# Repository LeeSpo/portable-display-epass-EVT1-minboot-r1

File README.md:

# Portable Display ePass

当前自研硬件为 **38 × 64 mm、四层 split-power 工程候选**，尚未放行生产。

- [打开当前 KiCad 工程与运行验证](portable-display/hardware/v1-WEB6-redesign/split-power-candidate/README_CN.md)
- [未完成项与实板验收](portable-display/hardware/v1-WEB6-redesign/split-power-candidate/OPEN_ISSUES_CN.md)
- [JLC 报价/预览包（未放行）](portable-display/hardware/v1-WEB6-redesign/split-power-candidate/verification/production_20261015/README_CN.md)
- [开发板学习资料](portable-display/hardware/v2-dev-board/README_CN.md)
- [项目进展、分支与旧稿恢复](portable-display/docs/PROJECT_STATUS_CN.md)

仓库只保留最新工程和验证包。旧版本、布线试验和历史报告通过 Git 历史追溯；不重写历史。

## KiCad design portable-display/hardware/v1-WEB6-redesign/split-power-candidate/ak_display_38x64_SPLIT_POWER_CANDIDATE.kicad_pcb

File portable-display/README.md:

# Portable Display

当前硬件为 38 × 64 mm 四层工程候选。电源冷启动、屏幕装配和实板功能尚未验收，**未放行投板、贴片或上电**。

| 入口 | 内容 |
|---|---|
| [当前自研工程](hardware/v1-WEB6-redesign/split-power-candidate/README_CN.md) | 原理图、PCB、本地库、约束及独立验证工具 |
| [当前工程验收记录](hardware/v1-WEB6-redesign/split-power-candidate/OPEN_ISSUES_CN.md) | 尚未关闭的工程与实板事项 |
| [开发板资料](hardware/v2-dev-board/README_CN.md) | YuzukiHD-Lizard 文档和图片，不是自研板的下一硬件版本 |
| [产品和屏幕资料](docs/README.md) | 屏幕规范、机械装配评估和项目状态 |
| [原始参考资料](reference/README.md) | 芯片/连接器资料、原始引脚表 |

工程使用 `${KIPRJMOD}` 本地库。运行命令见当前工程 README；无需历史硬件目录。

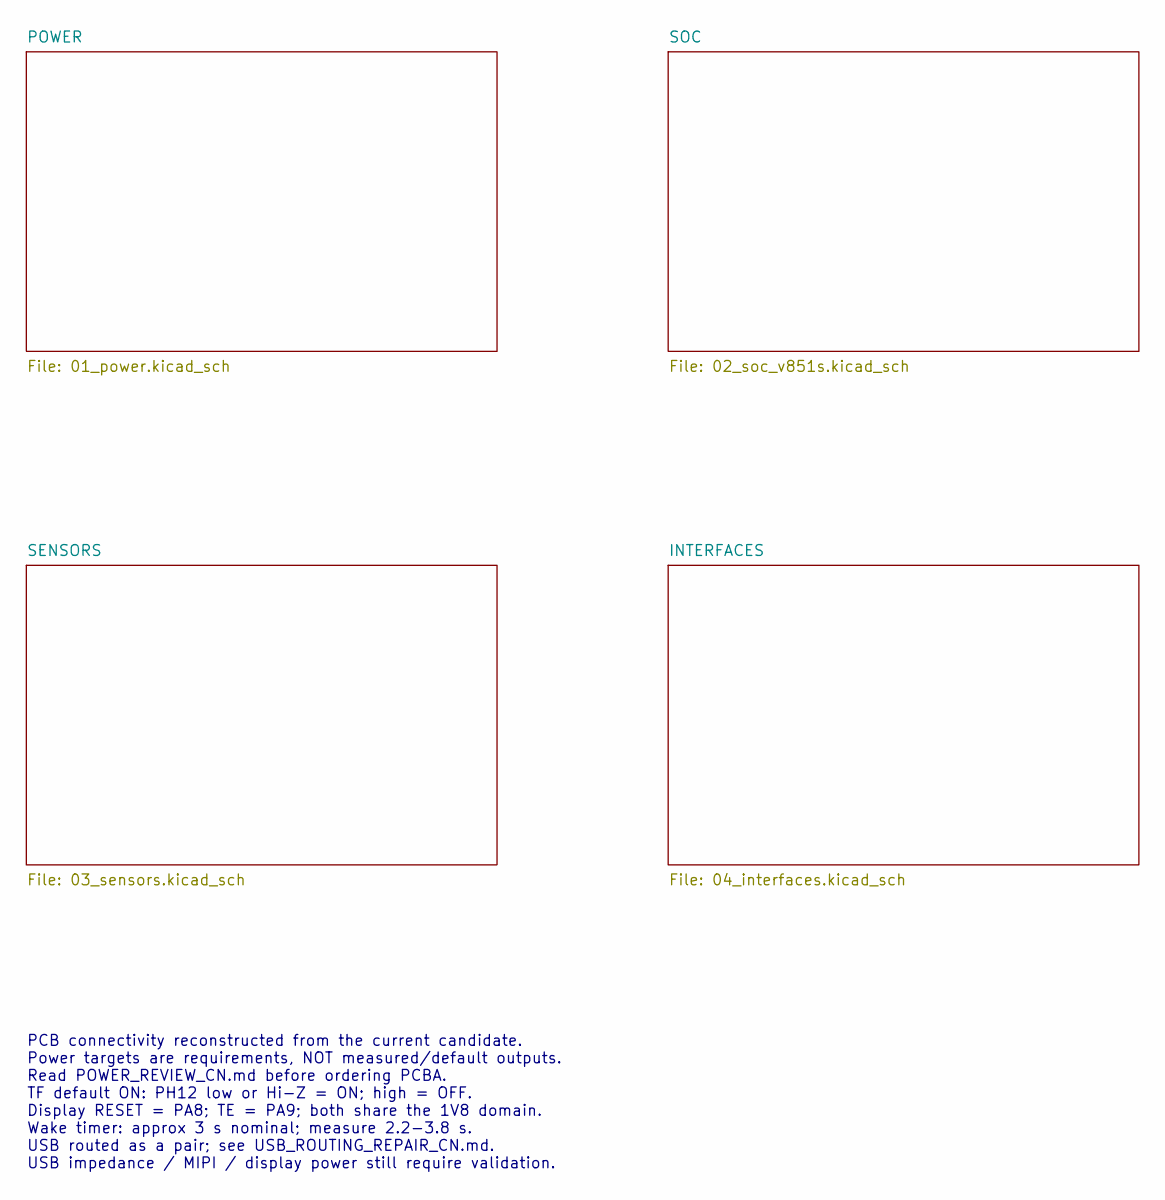
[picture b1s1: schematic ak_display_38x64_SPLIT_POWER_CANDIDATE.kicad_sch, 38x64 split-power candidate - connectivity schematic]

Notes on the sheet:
PCB connectivity reconstructed from the current candidate. Power targets are requirements, NOT measured/default outputs. Read POWER_REVIEW_CN.md before ordering PCBA. TF default ON: PH12 low or Hi-Z = ON; high = OFF. Display RESET = PA8; TE = PA9; both share the 1V8 domain. Wake timer: approx 3 s n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

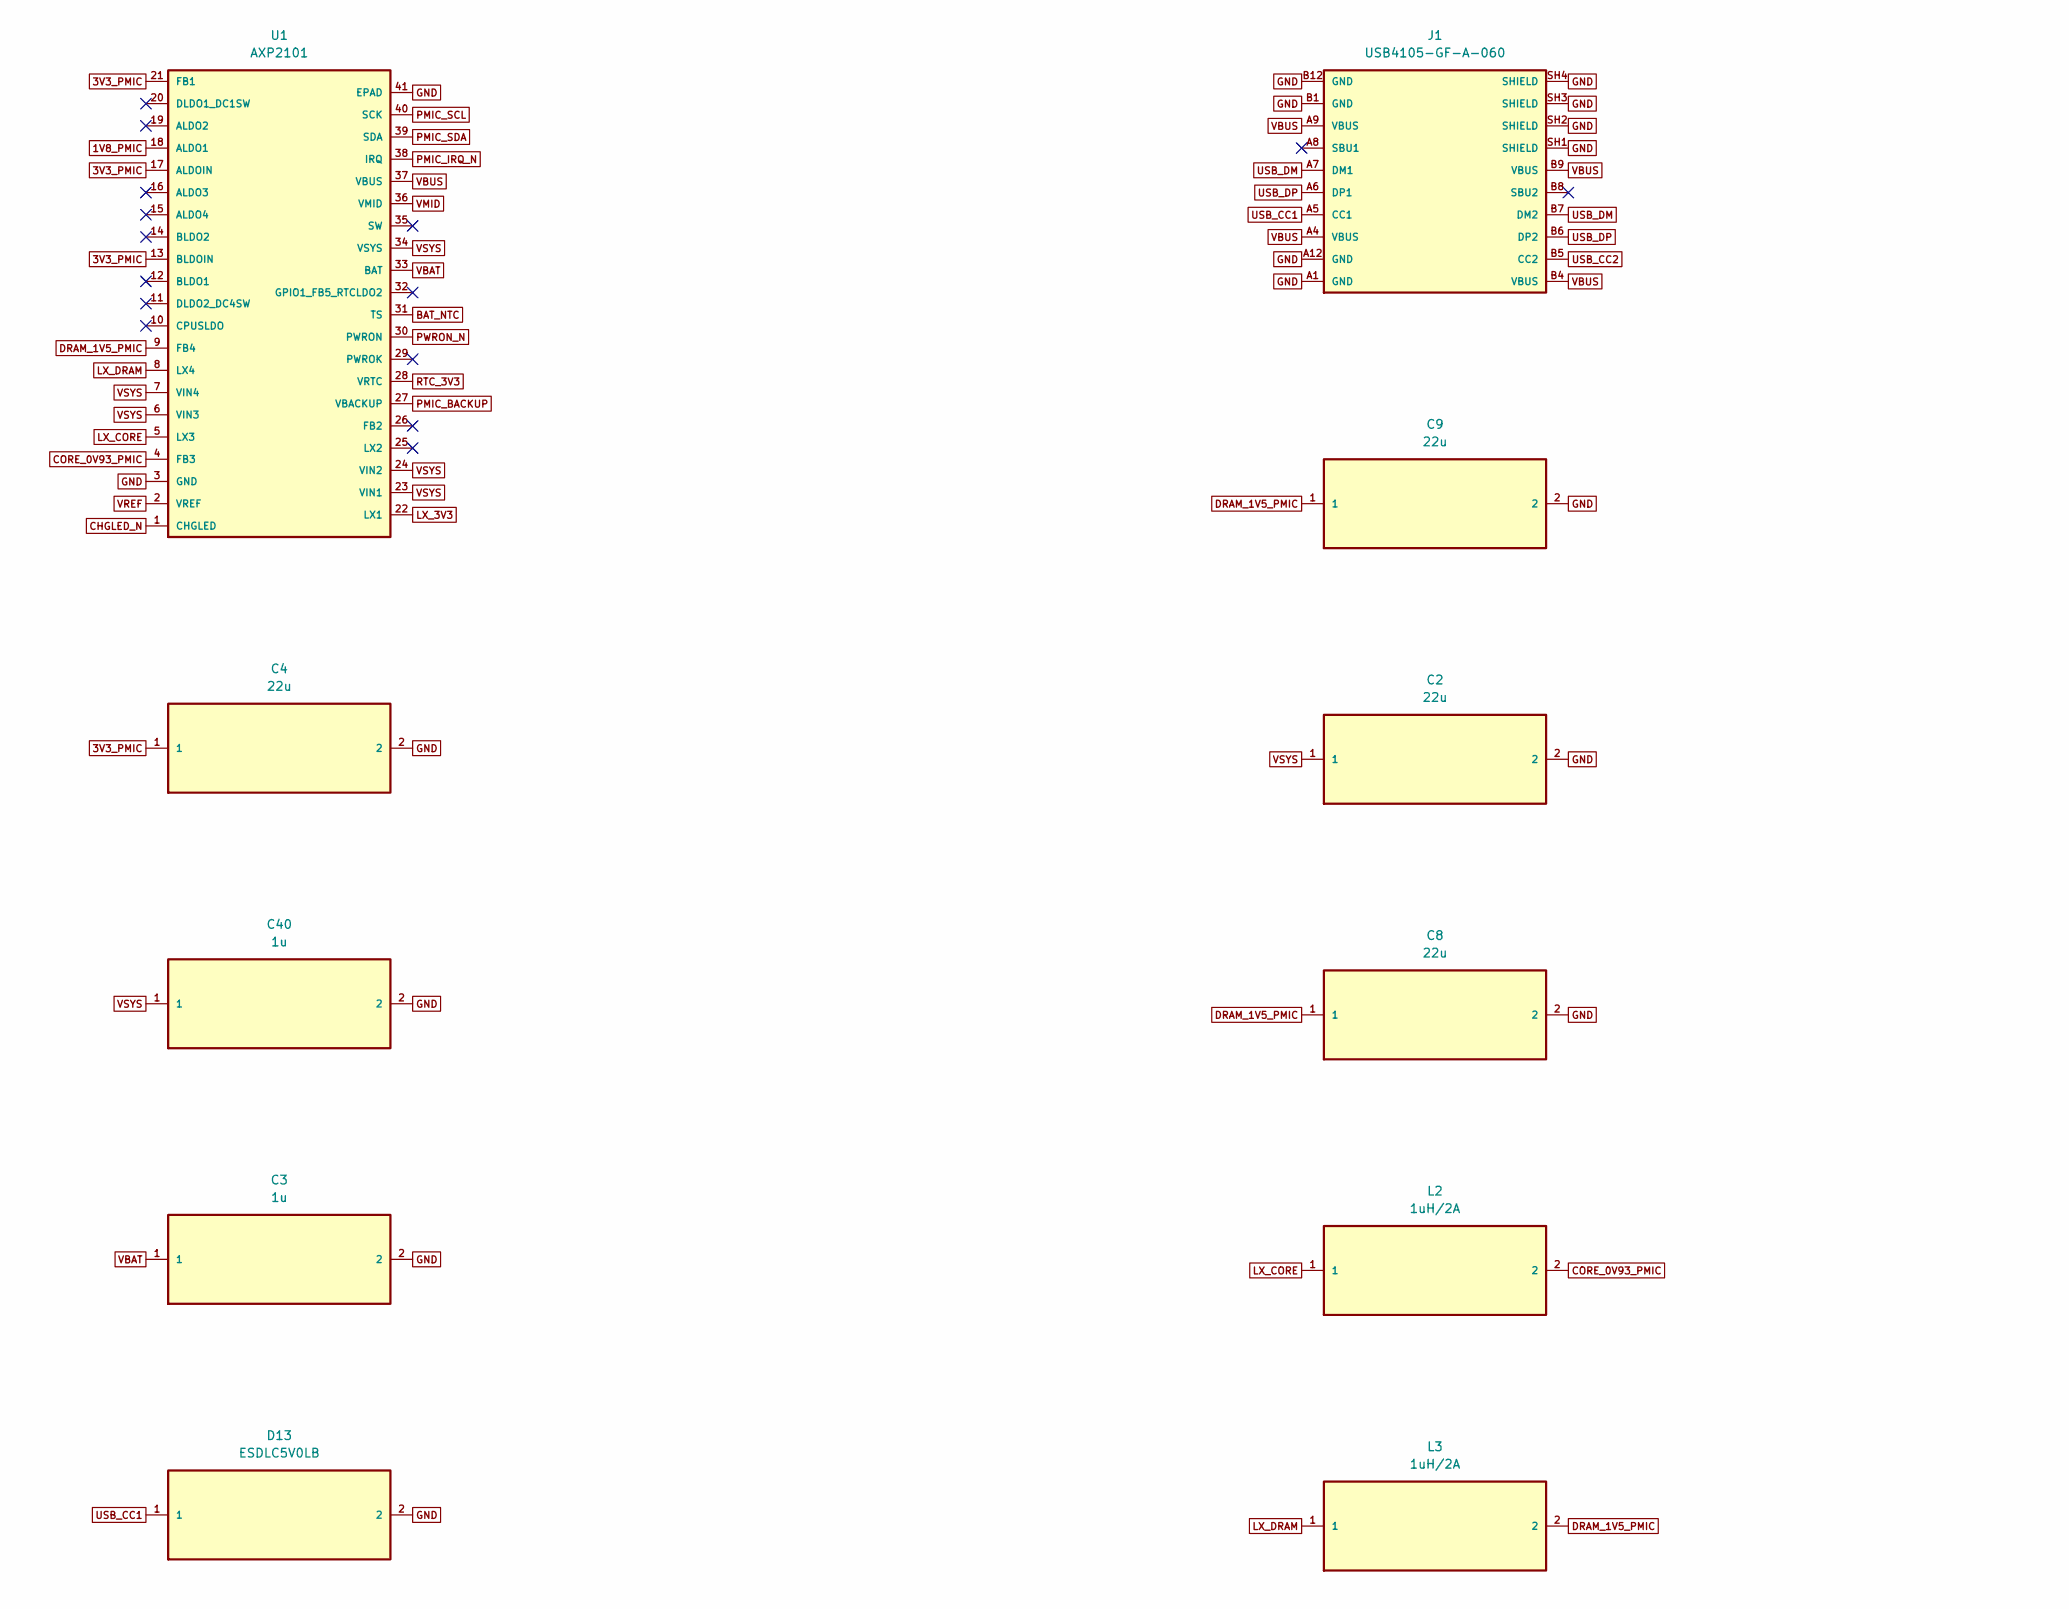
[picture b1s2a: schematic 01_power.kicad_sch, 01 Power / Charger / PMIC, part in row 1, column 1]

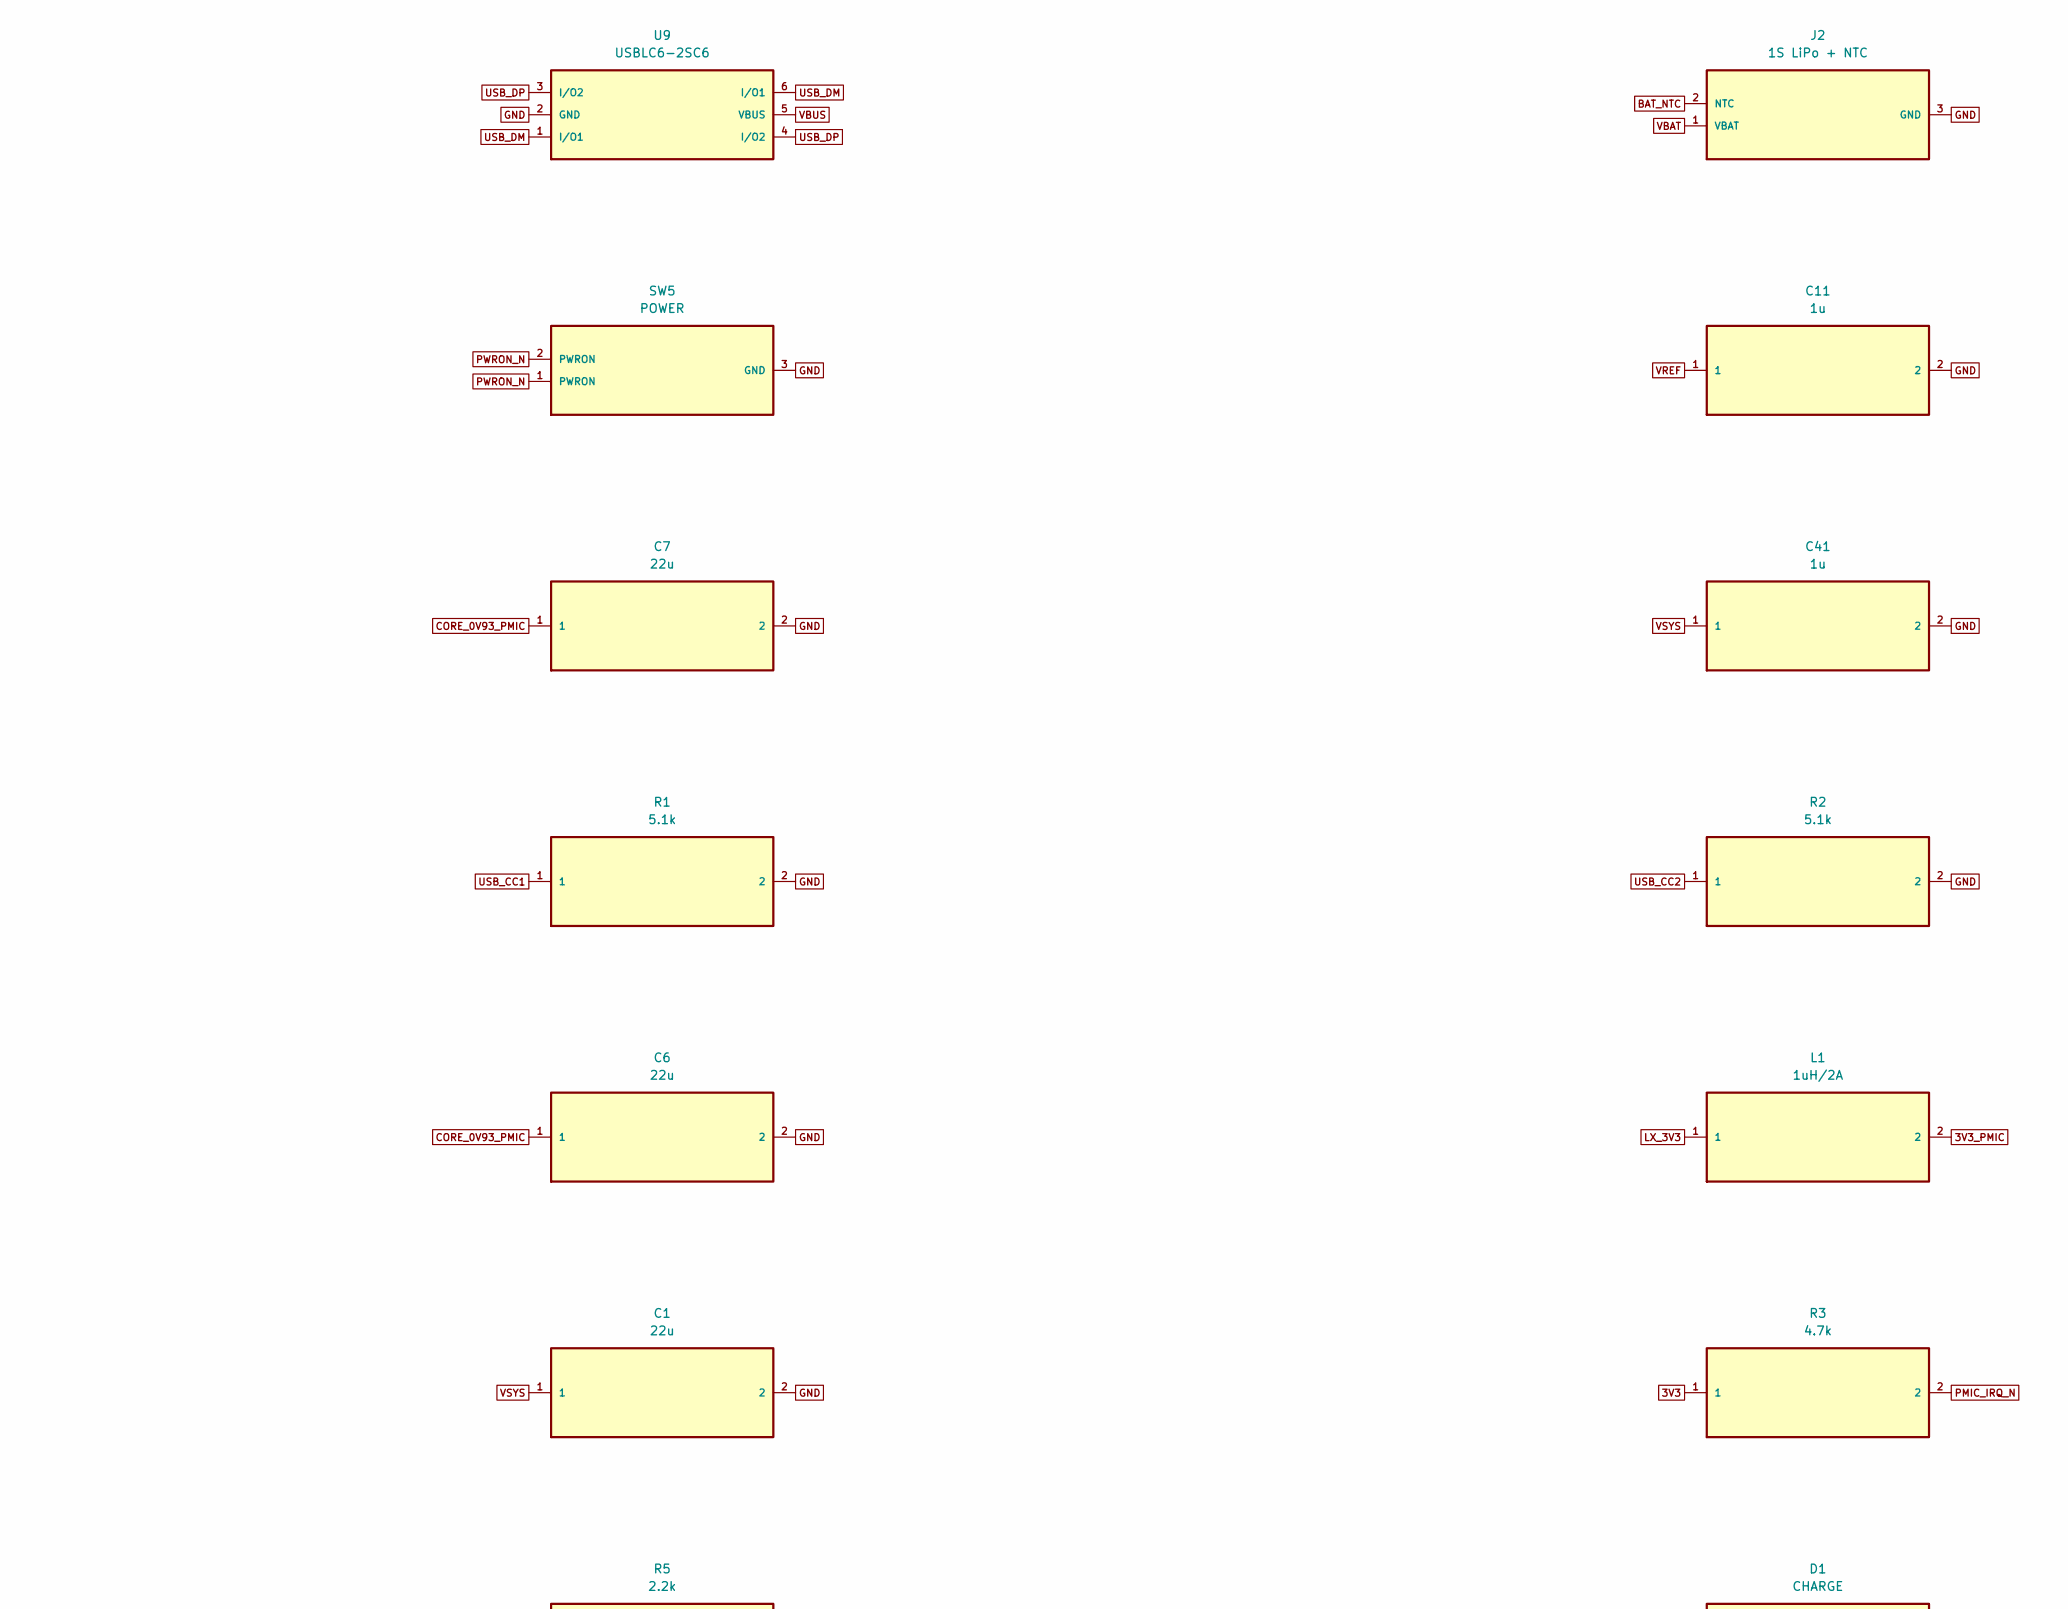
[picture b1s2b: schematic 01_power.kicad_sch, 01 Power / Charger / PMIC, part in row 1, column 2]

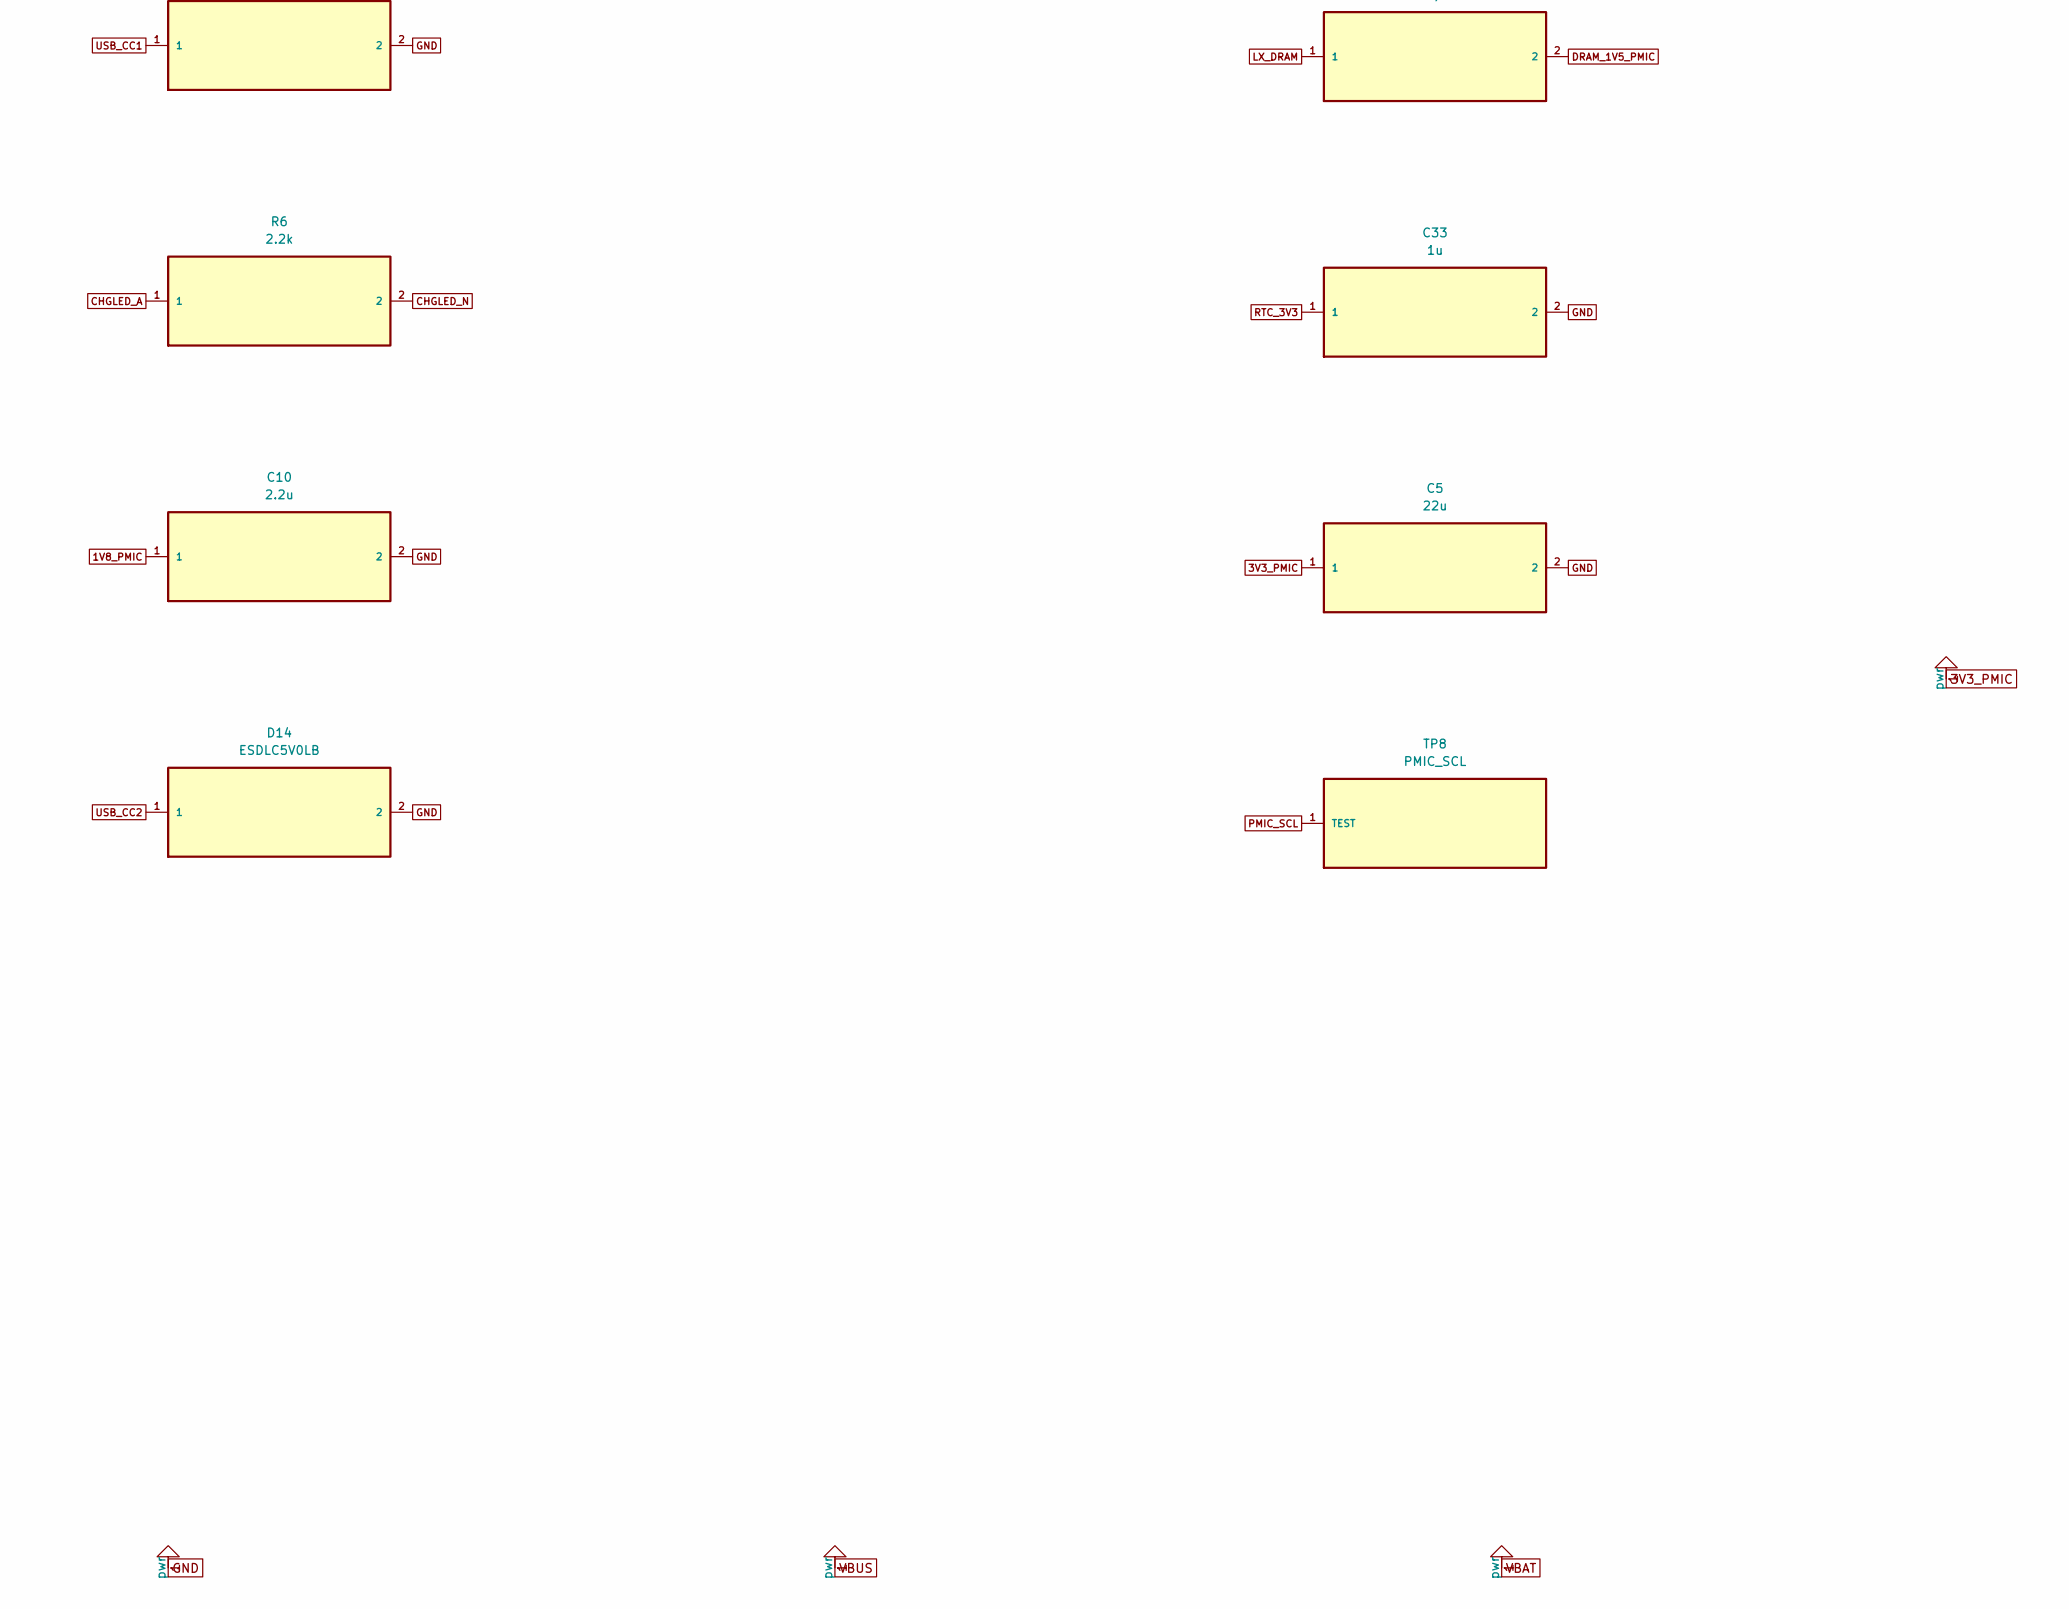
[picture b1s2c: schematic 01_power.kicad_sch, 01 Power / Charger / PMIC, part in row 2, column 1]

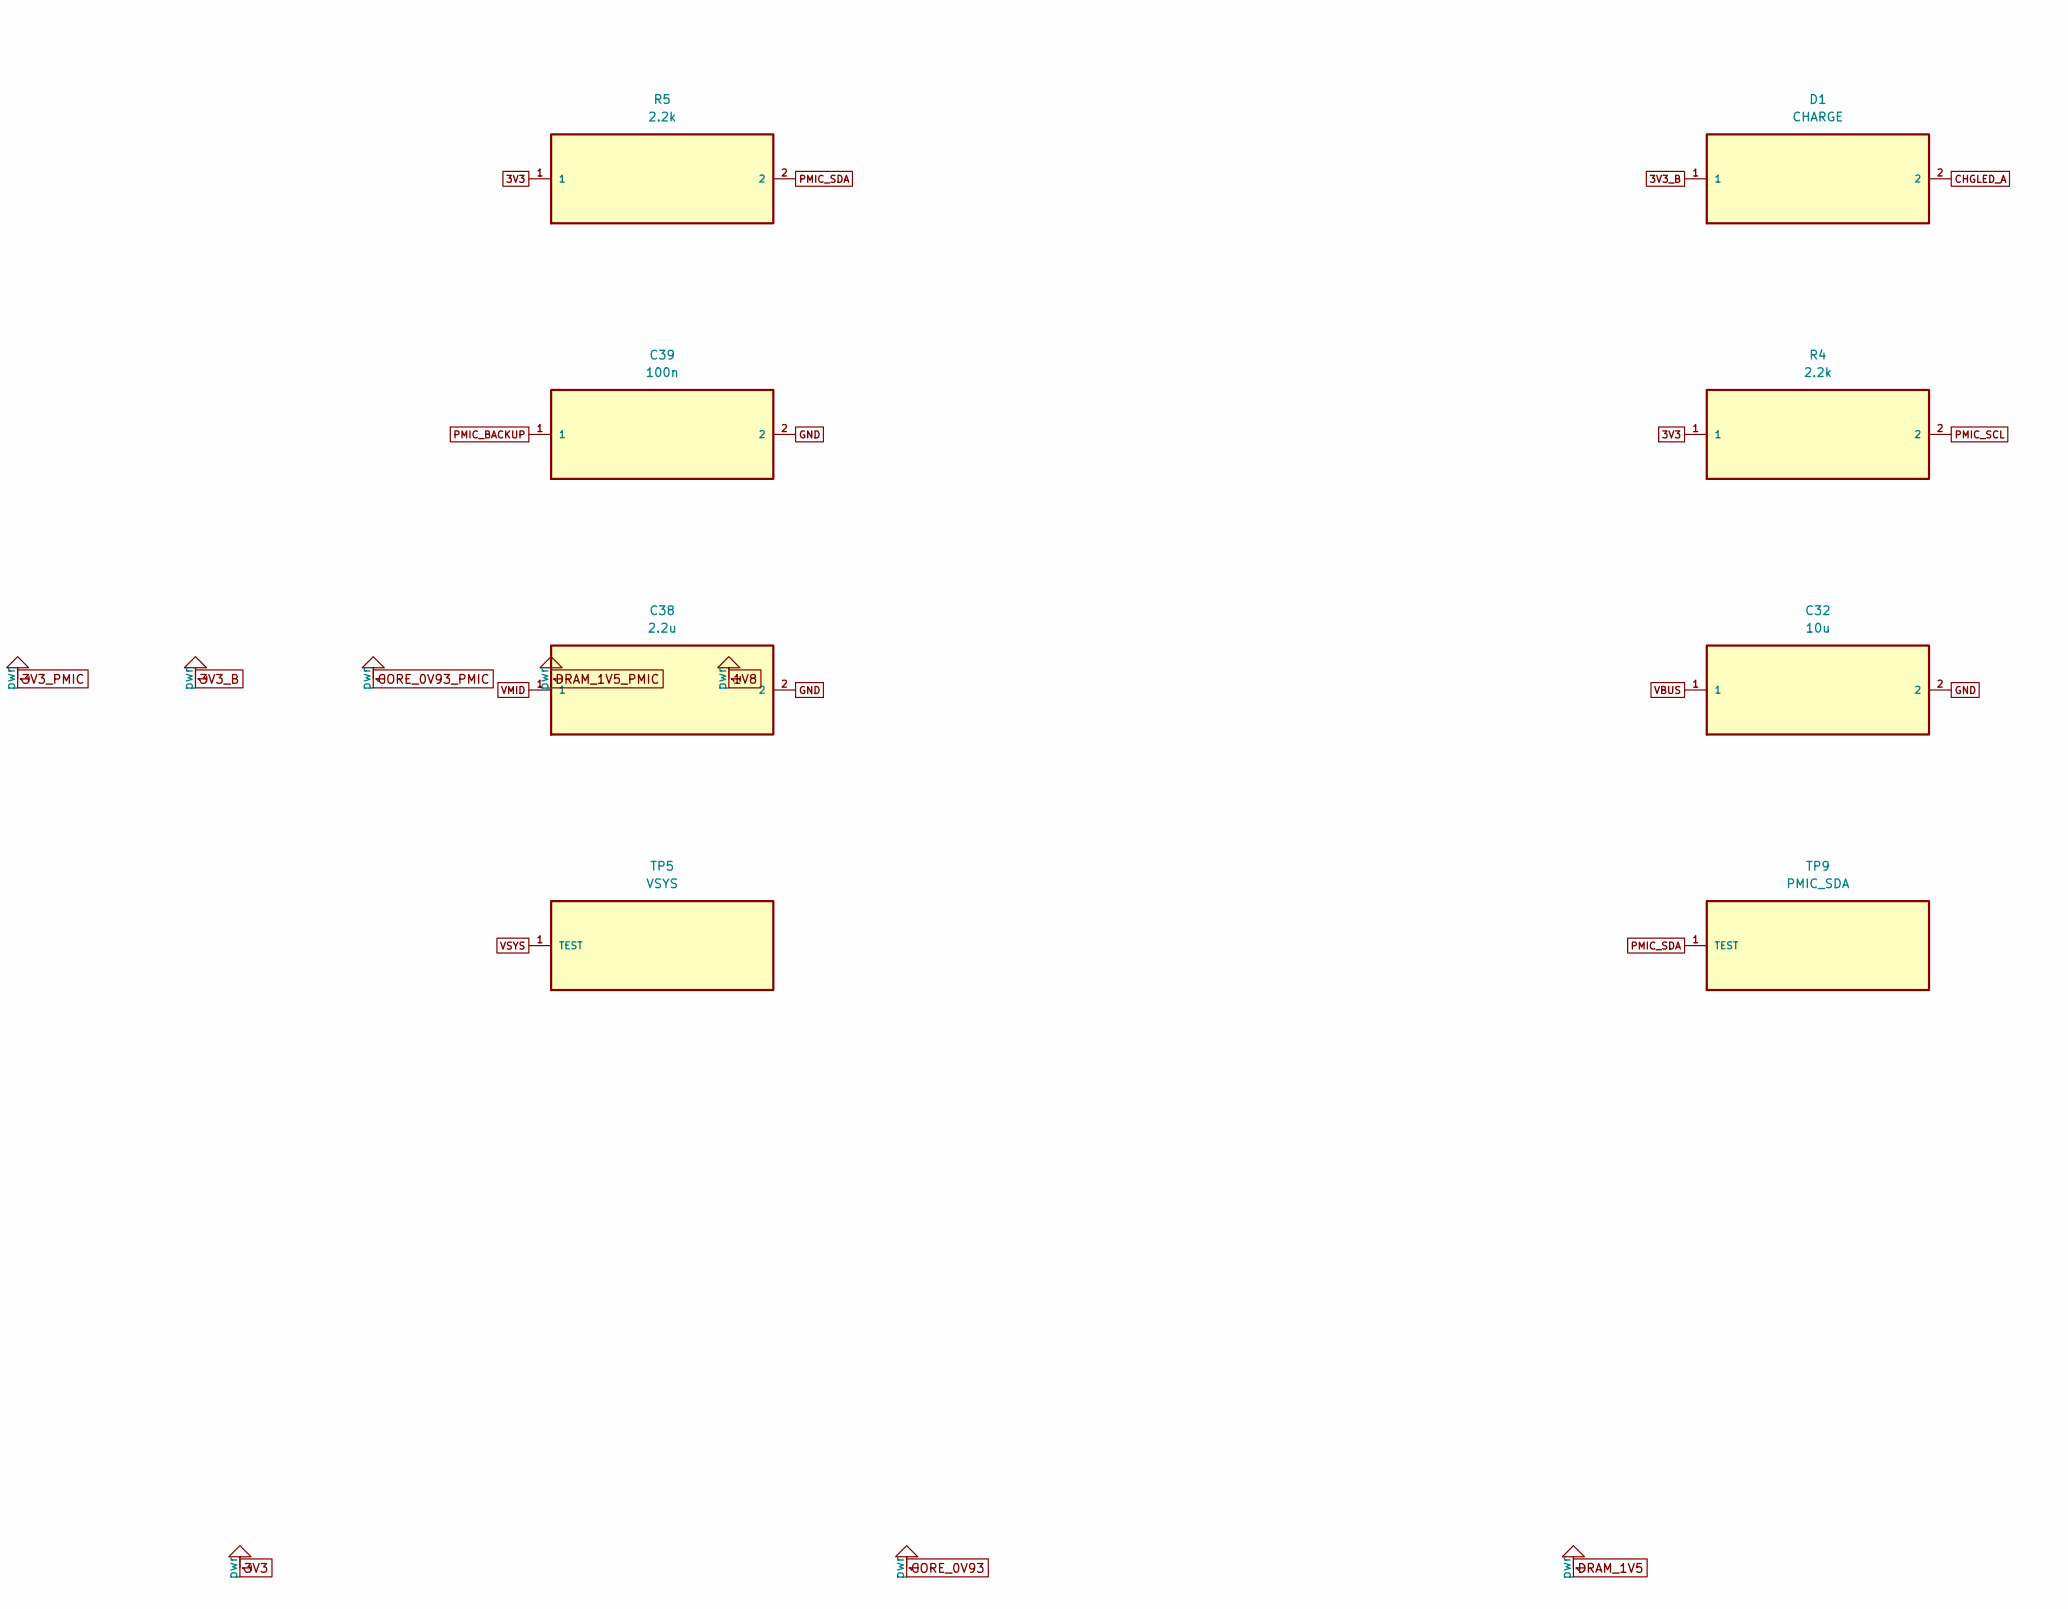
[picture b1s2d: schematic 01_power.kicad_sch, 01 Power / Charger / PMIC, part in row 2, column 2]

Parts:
C1, C2: 22u; 0603; MPN CL10A226MP8NUNE; LCSC C86295
C3, C11, C33, C40, C41: 1u; 0603; MPN CL10A105KB8NNNC; LCSC C15849
C4, C5, C6, C7, C8, C9: 22u; 0603; MPN CL10A226MQ8NRNC; LCSC C59461
C10, C38: 2.2u; 0603; MPN CL10A225KO8NNNC; LCSC C23630
C32: 10u; 0603; MPN CL10A106KP8NNNC; LCSC C19702
C39: 100n; 0402; MPN CL05B104KO5NNNC; LCSC C1525
D1: CHARGE; LED0603; MPN KT-0603G; LCSC C12624
D13, D14: ESDLC5V0LB; DFN1006-2; MPN ESDLC5V0LB; LCSC C20168172
J1: USB4105-GF-A-060; USB4105; MPN USB4105-GF-A-060; LCSC C3025063
J2: 1S LiPo + NTC; SH1.0_3P_RA; MPN ZX-SH1.0-3PWT; LCSC C7430445
L1, L2, L3: 1uH/2A; IND_2x2; MPN WPN201610H1R0MT; LCSC C97002
R1, R2: 5.1k; 0402; MPN 0402 5.1k 1%; LCSC C25905
R3: 4.7k; 0402; LCSC C25900
R4, R5, R6: 2.2k; 0402; LCSC C25879
SW5: POWER; SW_SIDE; MPN GT-TC072B-H045-L1; LCSC C5117859
TP5: VSYS; TestPoint_Pad_D1.0mm
TP8: PMIC_SCL; TestPoint_Pad_D1.0mm
TP9: PMIC_SDA; TestPoint_Pad_D1.0mm
U1: AXP2101; QFN40; MPN AXP2101; LCSC C3036461
U9: USBLC6-2SC6; USBLC6-2SC6_SOT23-6; MPN USBLC6-2SC6; LCSC C2827654

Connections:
1V8_PMIC: C10.1, U1.18 (ALDO1); also elsewhere on the board
3V3: R3.1, R4.1, R5.1; also elsewhere on the board
3V3_B: D1.1; also elsewhere on the board
3V3_PMIC: C4.1, C5.1, L1.2, U1.13 (BLDOIN), U1.17 (ALDOIN), U1.21 (FB1); also elsewhere on the board
BAT_NTC: J2.2 (NTC), U1.31 (TS)
CHGLED_A: D1.2, R6.1
CHGLED_N: R6.2, U1.1 (CHGLED)
CORE_0V93_PMIC: C6.1, C7.1, L2.2, U1.4 (FB3); also elsewhere on the board
DRAM_1V5_PMIC: C8.1, C9.1, L3.2, U1.9 (FB4); also elsewhere on the board
GND: C1.2, C2.2, C3.2, C4.2, C5.2, C6.2, C7.2, C8.2, C9.2, C10.2, C11.2, C32.2, C33.2, C38.2, C39.2, C40.2, C41.2, D13.2, D14.2, J1.A1 (GND), J1.A12 (GND), J1.B1 (GND), J1.B12 (GND), J1.SH1 (SHIELD), J1.SH2 (SHIELD), J1.SH3 (SHIELD), J1.SH4 (SHIELD), J2.3 (GND), R1.2, R2.2, SW5.3 (GND), U1.3 (GND), U1.41 (EPAD), U9.2 (GND); also elsewhere on the board
LX_3V3: L1.1, U1.22 (LX1)
LX_CORE: L2.1, U1.5 (LX3)
LX_DRAM: L3.1, U1.8 (LX4)
PMIC_BACKUP: C39.1, U1.27 (VBACKUP)
PMIC_IRQ_N: R3.2, U1.38 (IRQ); also elsewhere on the board
PMIC_SCL: R4.2, TP8.1 (TEST), U1.40 (SCK); also elsewhere on the board
PMIC_SDA: R5.2, TP9.1 (TEST), U1.39 (SDA); also elsewhere on the board
PWRON_N: SW5.1 (PWRON), SW5.2 (PWRON), U1.30 (PWRON); also elsewhere on the board
RTC_3V3: C33.1, U1.28 (VRTC); also elsewhere on the board
USB_CC1: D13.1, J1.A5 (CC1), R1.1
USB_CC2: D14.1, J1.B5 (CC2), R2.1
USB_DM: J1.A7 (DM1), J1.B7 (DM2), U9.1 (I/O1), U9.6 (I/O1); also elsewhere on the board
USB_DP: J1.A6 (DP1), J1.B6 (DP2), U9.3 (I/O2), U9.4 (I/O2); also elsewhere on the board
VBAT: C3.1, J2.1 (VBAT), U1.33 (BAT)
VBUS: C32.1, J1.A4 (VBUS), J1.A9 (VBUS), J1.B4 (VBUS), J1.B9 (VBUS), U1.37 (VBUS), U9.5 (VBUS)
VMID: C38.1, U1.36 (VMID)
VREF: C11.1, U1.2 (VREF)
VSYS: C1.1, C2.1, C40.1, C41.1, TP5.1 (TEST), U1.6 (VIN3), U1.7 (VIN4), U1.23 (VIN1), U1.24 (VIN2), U1.34 (VSYS)
